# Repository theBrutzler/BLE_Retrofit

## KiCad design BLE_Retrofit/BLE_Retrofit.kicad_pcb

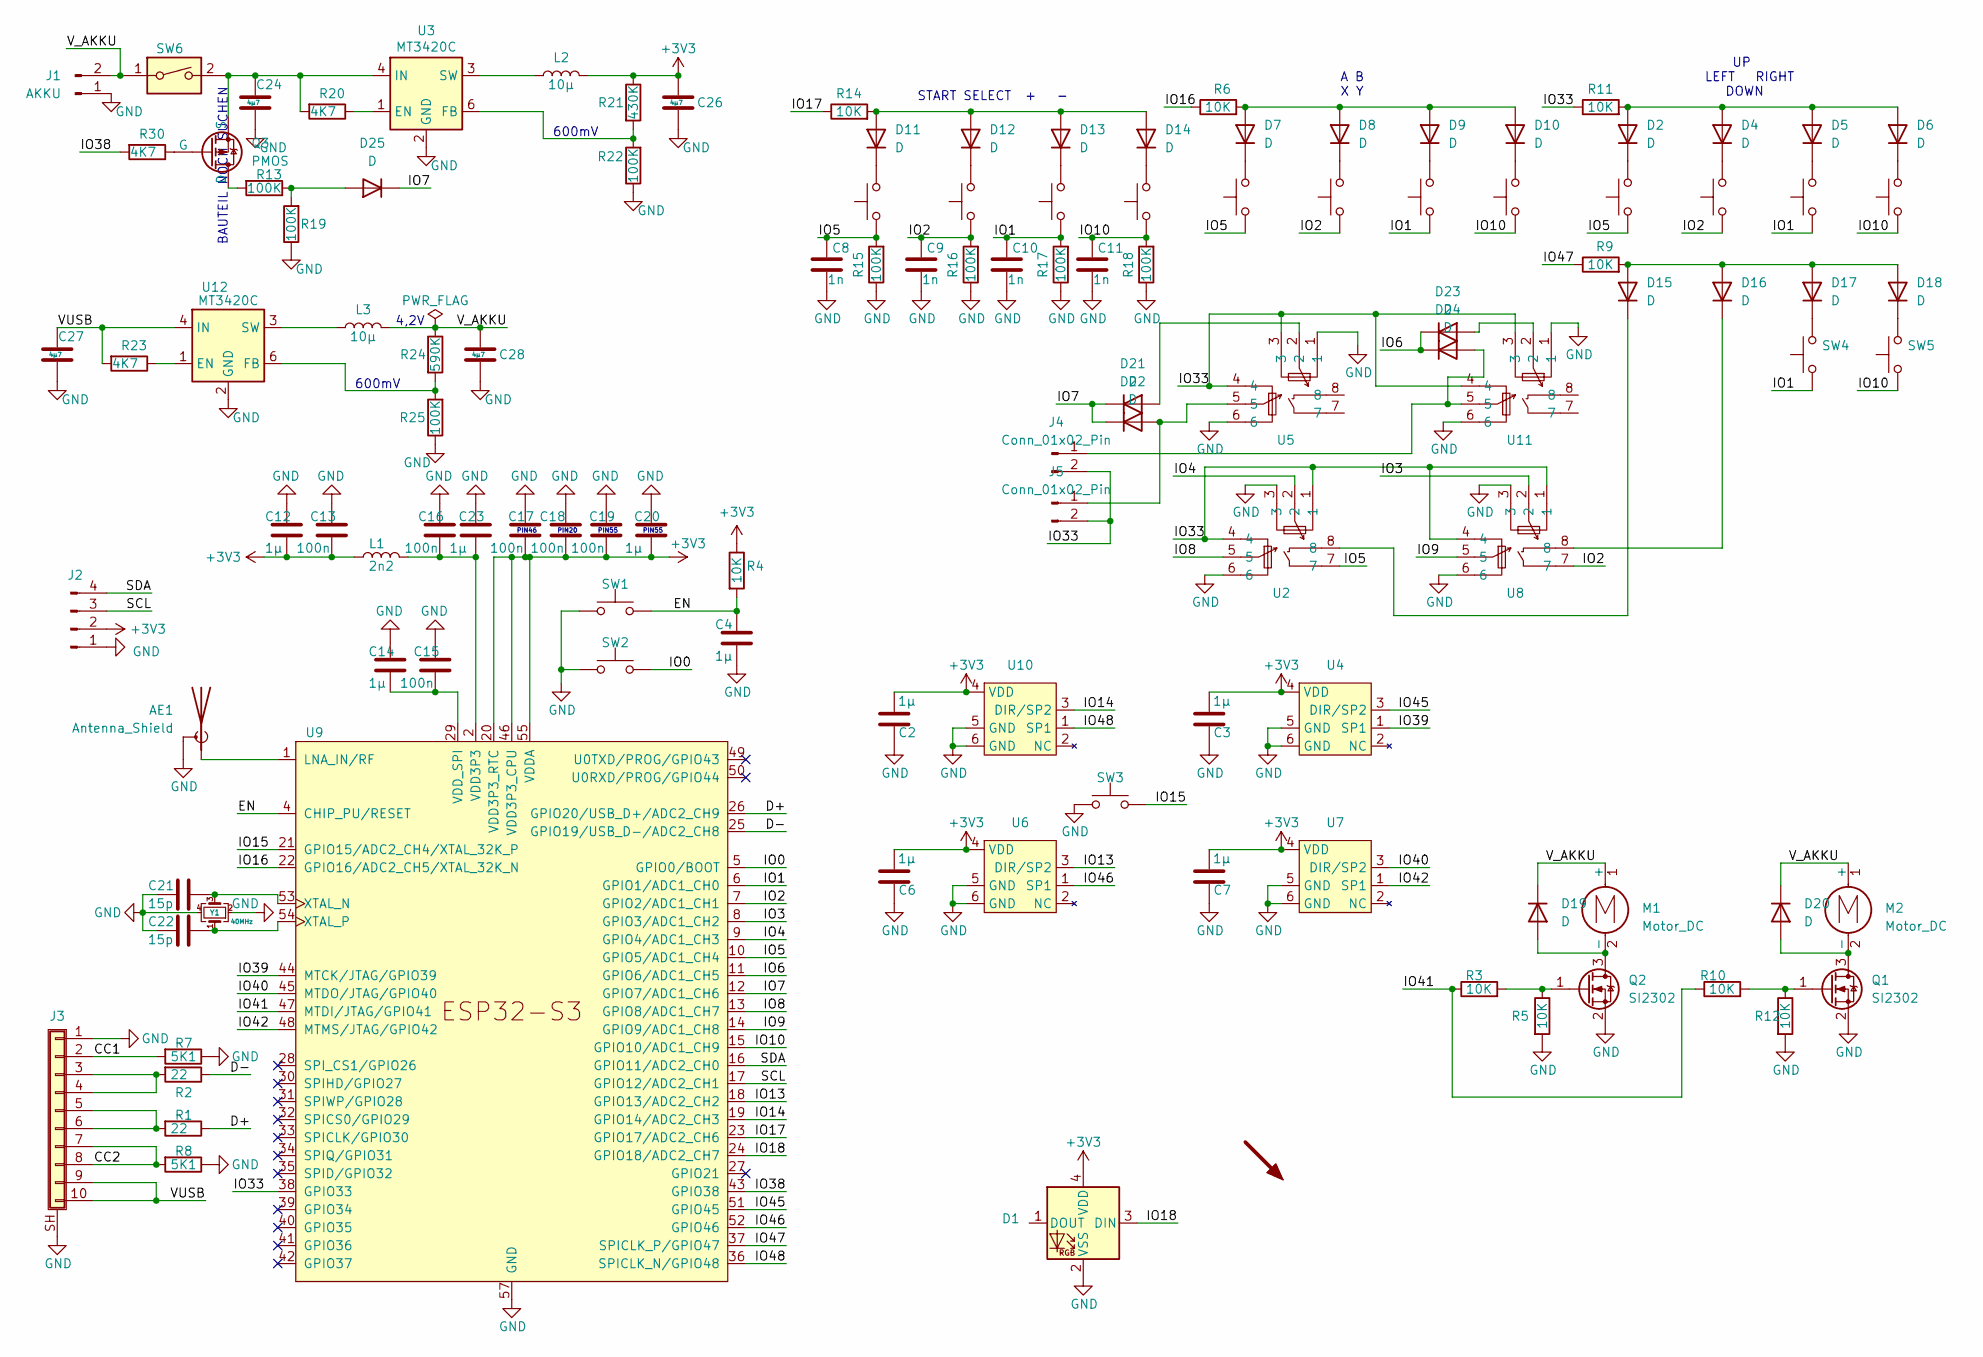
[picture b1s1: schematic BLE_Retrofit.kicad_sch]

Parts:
AE1: Antenna_Shield; Texas_SWRA117D_2.4GHz_Left; LCSC nc
C2, C3, C4, C6, C7: 1µ; R_0402_1005Metric
C8, C9, C10, C11: 1n; R_0402_1005Metric
C12, C14, C20, C23: 1µ; R_0402_1005Metric; LCSC C307413
C13, C15, C16, C17, C18, C19: 100n; R_0402_1005Metric; LCSC C1581
C21, C22: 15p; R_0402_1005Metric; LCSC C1548
C24, C26, C27, C28: 4µ7; C_0603_1608Metric; LCSC C415373
D1: WS2812B_Geaendertes_Symbol; LED_Cree-PLCC4_2x2mm_CCW; LCSC C965556
D2, D4, D5, D6, D7, D8, D9, D10, D11, D12, D13, D14, D15, D16, D17, D18, D19, D20, D21, D22, D23, D24, D25: D; D_SOD-123F
J1: AKKU; JST_PH_S2B-PH-SM4-TB_1x02-1MP_P2.00mm_Horizontal
J2: Conn_01x04_Pin; PinHeader_1x04_P2.54mm_Vertical
J3: Conn_01x10_Shielded; TE_1-1734839-0_1x10-1MP_P0.5mm_Horizontal
J4, J5: Conn_01x02_Pin; JST_PH_B2B-PH-K_1x02_P2.00mm_Vertical
L1: 2n2; L_0402_1005Metric; LCSC C27122
L2, L3: 10µ; L_Bourns-SRN4018; LCSC C520273
M1, M2: Motor_DC; BatteryHolder_Seiko_MS621F; LCSC C2759984
Q1, Q2: SI2302; SOT-23
Q3: PMOS; SOT-23
R1, R2: 22; R_0603_1608Metric
R3, R4, R5, R6, R9, R10, R11, R12, R14: 10K; R_0402_1005Metric
R7, R8: 5K1; R_0603_1608Metric
R13, R19, R22, R25: 100K; R_0603_1608Metric; LCSC C15458
R15, R16, R17, R18: 100K; R_0402_1005Metric
R20, R23, R30: 4K7; R_0603_1608Metric; LCSC C105428
R21: 430K; R_0603_1608Metric; LCSC C170597
R24: 590K; R_0603_1608Metric; LCSC C23208
SW1: SW_Push; SW_SPST_CK_RS282G05A3; LCSC C482003
SW2: SW_Push; SW_SPST_CK_RS282G05A3; LCSC C100056
SW3: SW_Push; SW_Panasonic_EVQP6xB55
SW4, SW5: SW_Push; SW_Tactile_SPST_Angled_PTS645Vx39-2LFS
SW6: SW_DIP_x01; SW_SPDT_PCM12; LCSC C3036445 C223846
SW16, SW17, SW18, SW19, SW20, SW21, SW22, SW23, SW24, SW25, SW26, SW27: SW_Push; RubberpadButton_250µ_250µ; LCSC C100056
U2, U8: SW_RKJXV122400R
U3, U12: MT3420C; SOT-23-6; LCSC C181741
U4, U6, U7, U10: SOT-23-6; LCSC C879630
U5, U11: FJ08K-S
U9: ESP32-S3; QFN-56-1EP_7x7mm_P0.4mm_EP5.6x5.6mm
Y1: 40MHz; Crystal_SMD_2016-4Pin_2.0x1.6mm; LCSC C424431

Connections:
+3V3: C2.2, C3.2, C6.2, C7.2, C12.2, C13.2, C17.2, C18.2, C19.2, C20.2, C26.1, D1.4 (VDD), J2.2, L1.1, L2.2, R4.1, R21.1, U4.4 (VDD), U6.4 (VDD), U7.4 (VDD), U9.20 (VDD3P3_RTC), U9.46 (VDD3P3_CPU), U9.55 (VDDA), U9.56 (VDDA), U10.4 (VDD)
/CC1: J3.2, R7.2
/CC2: J3.7, J3.8, R8.2
/D+: R1.1, U9.26 (GPIO20/USB_D+/ADC2_CH9)
/D-: R2.1, U9.25 (GPIO19/USB_D-/ADC2_CH8)
/EN: C4.1, R4.2, SW1.2, U9.4 (CHIP_PU/RESET)
/IO0: SW2.2, U9.5 (GPIO0/BOOT)
/IO1: C10.1, R17.2, SW4.1, SW19.1, SW23.1, SW27.1, U9.6 (GPIO1/ADC1_CH0)
/IO2: C9.1, R16.2, SW18.1, SW22.1, SW25.1, U8.7, U9.7 (GPIO2/ADC1_CH1)
/IO3: U8.2, U9.8 (GPIO3/ADC1_CH2)
/IO4: U2.2, U9.9 (GPIO4/ADC1_CH3)
/IO5: C8.1, R15.2, SW16.1, SW17.1, SW21.1, U2.7, U9.10 (GPIO5/ADC1_CH4)
/IO6: D23.1 (K), D24.1 (K), U9.11 (GPIO6/ADC1_CH5)
/IO7: D21.1 (K), D22.1 (K), D25.1 (K), U9.12 (GPIO7/ADC1_CH6)
/IO8: U2.5, U9.13 (GPIO8/ADC1_CH7)
/IO9: U8.5, U9.14 (GPIO9/ADC1_CH8)
/IO10: C11.1, R18.2, SW5.1, SW20.1, SW24.1, SW26.1, U9.15 (GPIO10/ADC1_CH9)
/IO13: U6.3 (DIR/SP2), U9.18 (GPIO13/ADC2_CH2)
/IO14: U9.19 (GPIO14/ADC2_CH3), U10.3 (DIR/SP2)
/IO15: SW3.2, U9.21 (GPIO15/ADC2_CH4/XTAL_32K_P)
/IO16: R6.1, U9.22 (GPIO16/ADC2_CH5/XTAL_32K_N)
/IO17: R14.1, U9.23 (GPIO17/ADC2_CH6)
/IO18: D1.3 (DIN), U9.24 (GPIO18/ADC2_CH7)
/IO33: J4.2, J5.2, R11.1, U2.1, U2.4, U5.3, U5.4, U8.1, U8.4, U9.38 (GPIO33), U11.3, U11.4
/IO38: R30.2, U9.43 (GPIO38)
/IO39: U4.1 (SP1), U9.44 (MTCK/JTAG/GPIO39)
/IO40: U7.3 (DIR/SP2), U9.45 (MTDO/JTAG/GPIO40)
/IO41: R3.1, R10.1, U9.47 (MTDI/JTAG/GPIO41)
/IO42: U7.1 (SP1), U9.48 (MTMS/JTAG/GPIO42)
/IO45: U4.3 (DIR/SP2), U9.51 (GPIO45)
/IO46: U6.1 (SP1), U9.52 (GPIO46)
/IO47: R9.1, U9.37 (SPICLK_P/GPIO47)
/IO48: U9.36 (SPICLK_N/GPIO48), U10.1 (SP1)
/SCL: J2.3, U9.17 (GPIO12/ADC2_CH1)
/SDA: J2.4, U9.16 (GPIO11/ADC2_CH0)
/VUSB: C27.1, J3.9, J3.10, R23.2, U12.4 (IN)
/V_AKKU: C28.1, D19.1 (K), D20.1 (K), J1.2, L3.2, M1.1 (+), M2.1 (+), R24.1, SW6.1
GND: AE1.2 (Shield), C2.1, C3.1, C4.2, C6.1, C7.1, C8.2, C9.2, C10.2, C11.2, C12.1, C13.1, C14.1, C15.1, C16.1, C17.1, C18.1, C19.1, C20.1, C21.2, C22.2, C23.1, C24.2, C26.2, C27.2, C28.2, D1.2 (VSS), J1.1, J2.1, J3.1, J3.MP, J3.SH (Shield), Q1.2 (S), Q2.2 (S), R5.2, R7.1, R8.1, R12.2, R15.1, R16.1, R17.1, R18.1, R19.1, R22.1, R25.1, SW1.1, SW2.1, SW3.1, U2.3, U2.6, U3.2 (GND), U4.5 (GND), U4.6 (GND), U5.1, U5.6, U6.5 (GND), U6.6 (GND), U7.5 (GND), U7.6 (GND), U8.3, U8.6, U9.57 (GND), U10.5 (GND), U10.6 (GND), U11.1, U11.6, U12.2 (GND), Y1.2, Y1.4
unnamed: AE1.1 (A), U9.1 (LNA_IN/RF)
unnamed: D2.2 (A), D4.2 (A), D5.2 (A), D6.2 (A), R11.2
unnamed: D2.1 (K), SW16.2
unnamed: D4.1 (K), SW25.2
unnamed: D5.1 (K), SW27.2
unnamed: D6.1 (K), SW26.2
unnamed: D7.1 (K), SW21.2
unnamed: D8.1 (K), SW22.2
unnamed: D9.1 (K), SW23.2
unnamed: D7.2 (A), D8.2 (A), D9.2 (A), D10.2 (A), R6.2
unnamed: D10.1 (K), SW24.2
unnamed: D11.2 (A), D12.2 (A), D13.2 (A), D14.2 (A), R14.2
unnamed: D11.1 (K), SW17.2
unnamed: D12.1 (K), SW18.2
unnamed: D13.1 (K), SW19.2
unnamed: D14.1 (K), SW20.2
unnamed: D15.2 (A), D16.2 (A), D17.2 (A), D18.2 (A), R9.2
unnamed: D15.1 (K), U2.8
unnamed: D16.1 (K), U8.8
unnamed: D17.1 (K), SW4.2
unnamed: D18.1 (K), SW5.2
unnamed: D19.2 (A), M1.2 (-), Q2.3 (D)
unnamed: D20.2 (A), M2.2 (-), Q1.3 (D)
unnamed: D21.2 (A), U5.2
unnamed: D22.2 (A), J5.1, U5.5
unnamed: D23.2 (A), U11.2
unnamed: D24.2 (A), J4.1, U11.5
unnamed: D25.2 (A), R13.1, R19.2
unnamed: J3.3, J3.4, R2.2
unnamed: J3.5, J3.6, R1.2
unnamed: Q1.1 (G), R10.2, R12.1
unnamed: Q2.1 (G), R3.2, R5.1
unnamed: Q3.1 (D), R13.2
unnamed: Q3.2 (G), R30.1
unnamed: C24.1, Q3.3 (S), R20.2, SW6.2, U3.4 (IN)
unnamed: R20.1, U3.1 (EN)
unnamed: R21.2, R22.2, U3.6 (FB)
unnamed: L2.1, U3.3 (SW)
unnamed: C14.2, C15.2, U9.29 (VDD_SPI)
unnamed: C21.1, U9.53 (XTAL_N), Y1.3
unnamed: C22.1, U9.54 (XTAL_P), Y1.1
unnamed: R23.1, U12.1 (EN)
unnamed: R24.2, R25.2, U12.6 (FB)
unnamed: L3.1, U12.3 (SW)
VDD3P3: C16.2, C23.2, L1.2, U9.2 (VDD3P3), U9.3 (VDD3P3)

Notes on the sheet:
PIN46
PIN20
BAUTEIL NOCH SUCHEN
A B X Y
600mV
PIN55
UP LEFT RIGHT DOWN
4,2V
START SELECT + -

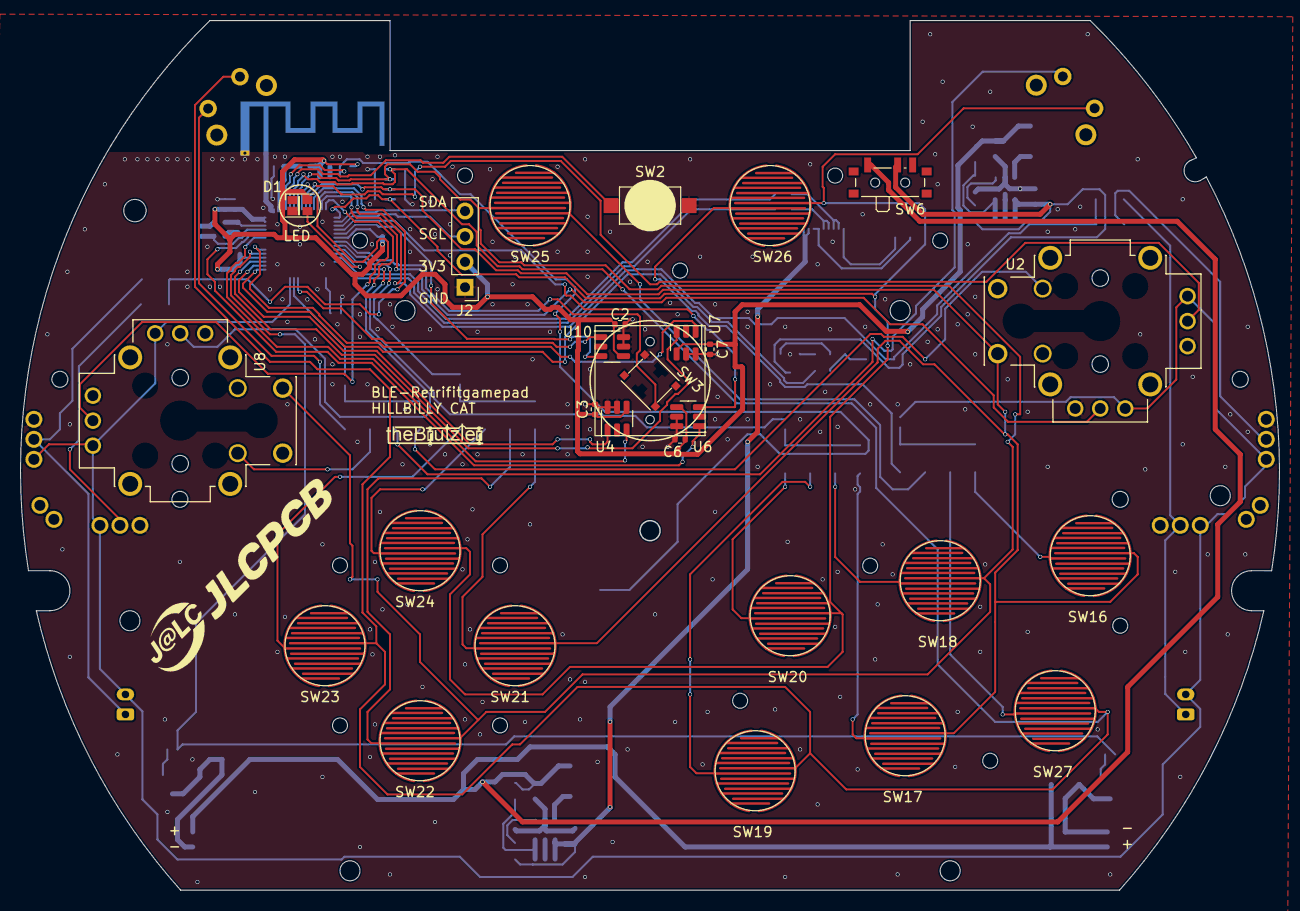
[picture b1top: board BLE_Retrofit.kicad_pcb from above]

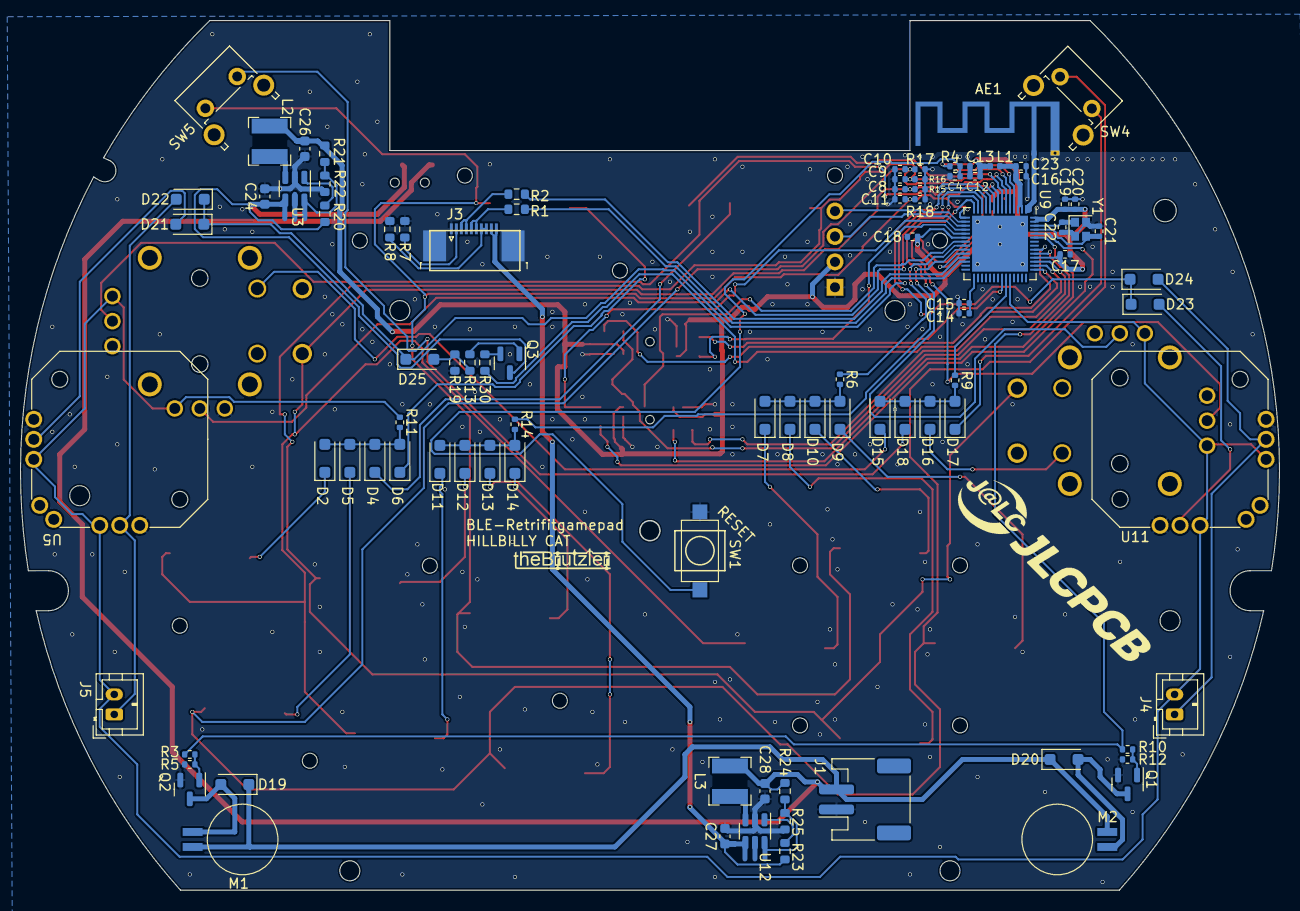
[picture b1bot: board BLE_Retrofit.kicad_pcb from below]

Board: 2 copper layers, 125.8 x 86.9 mm, 119 parts (92 on the bottom side), 83 nets.

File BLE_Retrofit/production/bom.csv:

Designator,Footprint,Quantity,Value,LCSC Part #
AE1,Texas_SWRA117D_2.4GHz_Left,1,Antenna_Shield,nc
"C10, C11, C8, C9",0402,4,1n,
"C12, C14, C2, C20, C23, C3, C4, C6, C7",0402,9,1µ,C307413
"C13, C15, C16, C17, C18, C19",0402,6,100n,C1581
"C21, C22",0402,2,15p,C1548
"C24, C26, C27, C28",0603,4,4µ7,C415373
D1,LED_Cree-PLCC4_2x2mm_CCW,1,WS2812B_Geaendertes_Symbol,C965556
"D10, D11, D12, D13, D14, D15, D16, D17, D18, D19, D2, D20, D21, D22, D23, D24, D25, D4, D5, D6, D7, D8, D9",D_SOD-123F,23,D,
J1,JST_PH_S2B-PH-SM4-TB_1x02-1MP_P2.00mm_Horizontal,1,AKKU,
J2,PinHeader_1x04_P2.54mm_Vertical,1,Conn_01x04_Pin,
J3,TE_1-1734839-0_1x10-1MP_P0.5mm_Horizontal,1,Conn_01x10_Shielded,
"J4, J5",JST_PH_B2B-PH-K_1x02_P2.00mm_Vertical,2,Conn_01x02_Pin,
L1,0402,1,2n2,C27122
"L2, L3",L_Bourns-SRN4018,2,10µ,C520273
"M1, M2",BatteryHolder_Seiko_MS621F,2,Motor_DC,C2759984
"Q1, Q2",SOT-23,2,SI2302,
Q3,SOT-23,1,PMOS,
"R1, R2",0603,2,22,
"R10, R11, R12, R14, R3, R4, R5, R6, R9",0402,9,10K,
"R13, R19, R22, R25",0603,4,100K,C15458
"R15, R16, R17, R18",0402,4,100K,
"R20, R23, R30",0603,3,4K7,C105428
R21,0603,1,430K,C170597
R24,0603,1,590K,C23208
"R7, R8",0603,2,5K1,
"SW1, SW2",SW_SPST_CK_RS282G05A3,2,SW_Push,C482003
"SW16, SW17, SW18, SW19, SW20, SW21, SW22, SW23, SW24, SW25, SW26, SW27",RubberpadButton_250µ_250µ,12,SW_Push,C100056
SW3,SW_Panasonic_EVQP6xB55,1,SW_Push,
"SW4, SW5",SW_Tactile_SPST_Angled_PTS645Vx39-2LFS,2,SW_Push,
SW6,SW_SPDT_PCM12,1,SW_DIP_x01,C3036445 C223846
"U10, U4, U6, U7",SOT-23-6,4,~,C879630
"U11, U5",FJ08K-S,2,~,
"U12, U3",SOT-23-6,2,MT3420C,C181741
"U2, U8",SW_RKJXV122400R,2,~,
U9,QFN-56-1EP_7x7mm_P0.4mm_EP5.6x5.6mm,1,ESP32-S3,
Y1,Crystal_SMD_2016-4Pin_2.0x1.6mm,1,40MHz,C424431

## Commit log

2024-07-16 Initial upload
